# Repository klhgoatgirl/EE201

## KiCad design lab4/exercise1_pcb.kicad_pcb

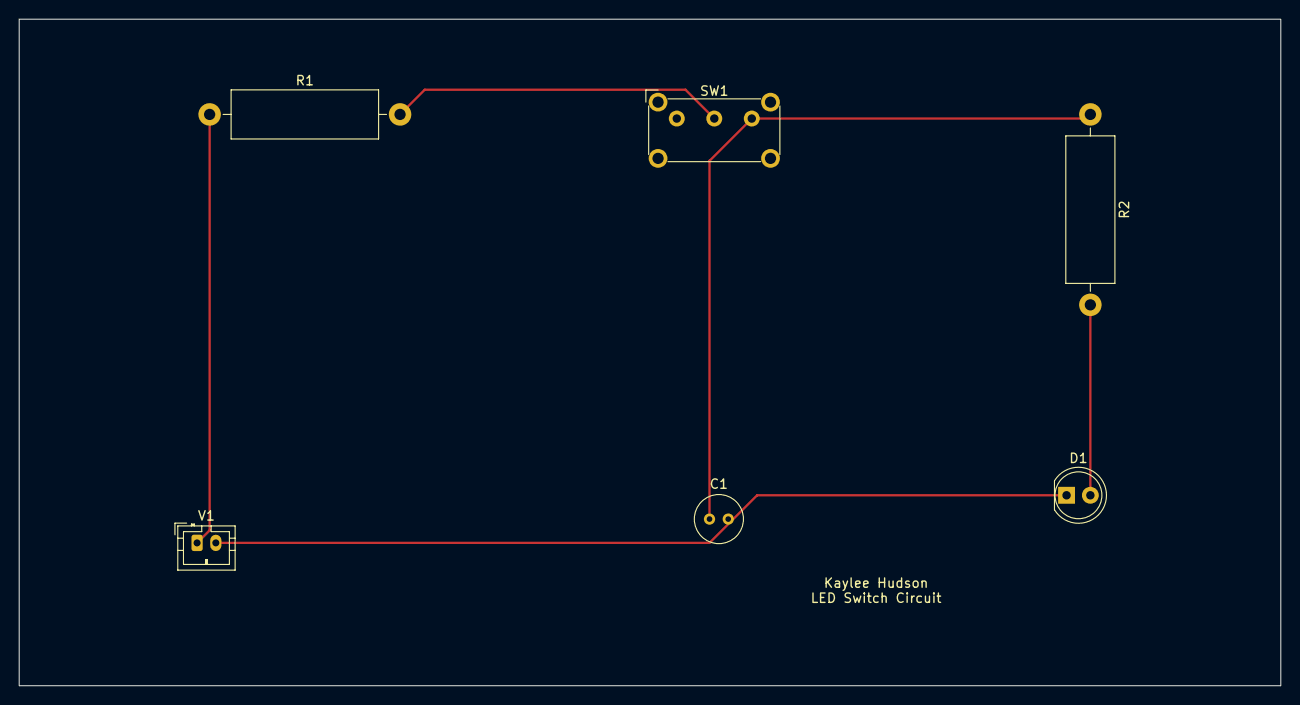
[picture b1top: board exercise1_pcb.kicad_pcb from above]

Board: 2 copper layers, 134.6 x 71.1 mm, 6 parts (0 on the bottom side), 5 nets.

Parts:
C1: 4.7 µm; C_Radial_D5.0mm_H5.0mm_P2.00mm
D1: LED; LED_D5.0mm
R1: 2.2 kΩ; R_Axial_DIN0516_L15.5mm_D5.0mm_P20.32mm_Horizontal
R2: 20 kΩ; R_Axial_DIN0516_L15.5mm_D5.0mm_P20.32mm_Horizontal
SW1: SW_SPDT; SW_E-Switch_EG1224_SPDT_Angled
V1: 9V; JST_PH_B2B-PH-K_1x02_P2.00mm_Vertical

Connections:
unnamed: C1.1, R2.1, SW1.3 (C)
unnamed: C1.2, D1.1 (K), V1.2
unnamed: D1.2 (A), R2.2
unnamed: R1.1, V1.1
unnamed: R1.2, SW1.2 (B)

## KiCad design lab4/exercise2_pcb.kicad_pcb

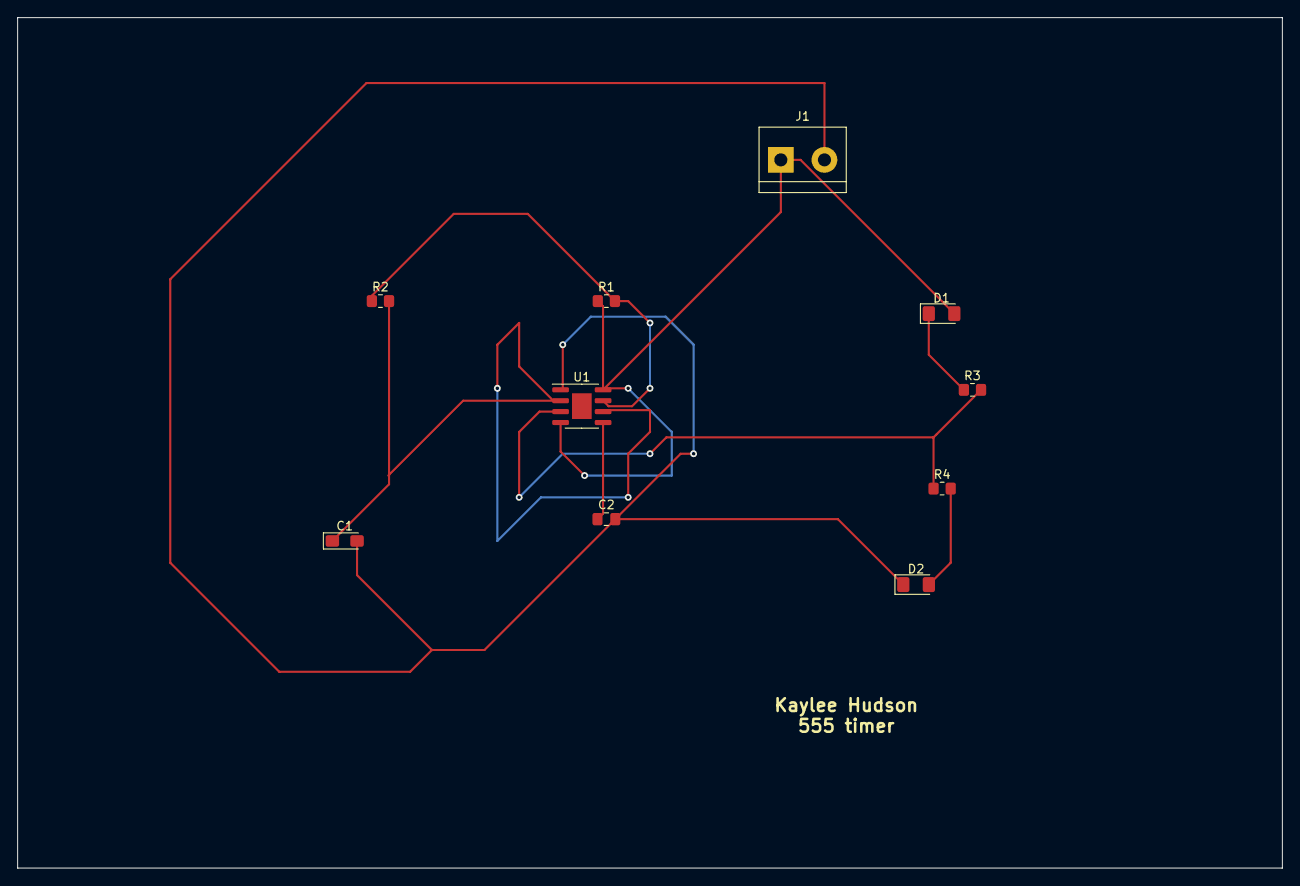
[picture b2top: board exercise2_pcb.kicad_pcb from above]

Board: 2 copper layers, 147.3 x 99.1 mm, 10 parts (0 on the bottom side), 8 nets.

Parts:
C1: 10µF; CP_EIA-3216-18_Kemet-A_Pad1.58x1.35mm_HandSolder
C2: 0.01µF; C_0805_2012Metric_Pad1.18x1.45mm_HandSolder
D1, D2: LED; LED_1206_3216Metric_Pad1.42x1.75mm_HandSolder
J1: Conn_01x02_Male; TerminalBlock_bornier-2_P5.08mm
R1, R3, R4: 1k; R_0805_2012Metric_Pad1.20x1.40mm_HandSolder
R2: 10k; R_0805_2012Metric_Pad1.20x1.40mm_HandSolder
U1: NE555D; SOIC-8-1EP_3.9x4.9mm_P1.27mm_EP2.29x3mm

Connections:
+9V: D1.2 (A), J1.1, R1.1, U1.4 (R), U1.8 (VCC)
/pin_2: C1.1, R2.2, U1.2 (TR), U1.6 (THR)
/pin_3: R3.2, R4.1, U1.3 (Q)
/pin_7: R1.2, R2.1, U1.7 (DIS)
GND: C1.2, C2.2, D2.1 (K), J1.2, U1.1 (GND)
unnamed: C2.1, U1.5 (CV)
unnamed: D2.2 (A), R4.2
unnamed: D1.1 (K), R3.1

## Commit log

2023-01-13 adds aboutMe
2023-01-13 deleted aboutMe
2023-01-13 add aboutMe
2023-01-20 Added arduino docs
2023-01-27 push kicad exercises
2023-02-03 added soldering images
2023-02-03 added soldering images - resized
2023-02-03 added more soldering images
2023-02-10 Added PCB layout documents
2023-02-17 Added gerber files
2023-03-15 Added finished arduometer design
